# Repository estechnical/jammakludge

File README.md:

# JammaKludge

A simple PCB to insert between Jamma PCBs and the jamma connector to break out test points.

Also provides a kludge space for video filters/impedance matching used to fix ghosting.

That's Jammawang!

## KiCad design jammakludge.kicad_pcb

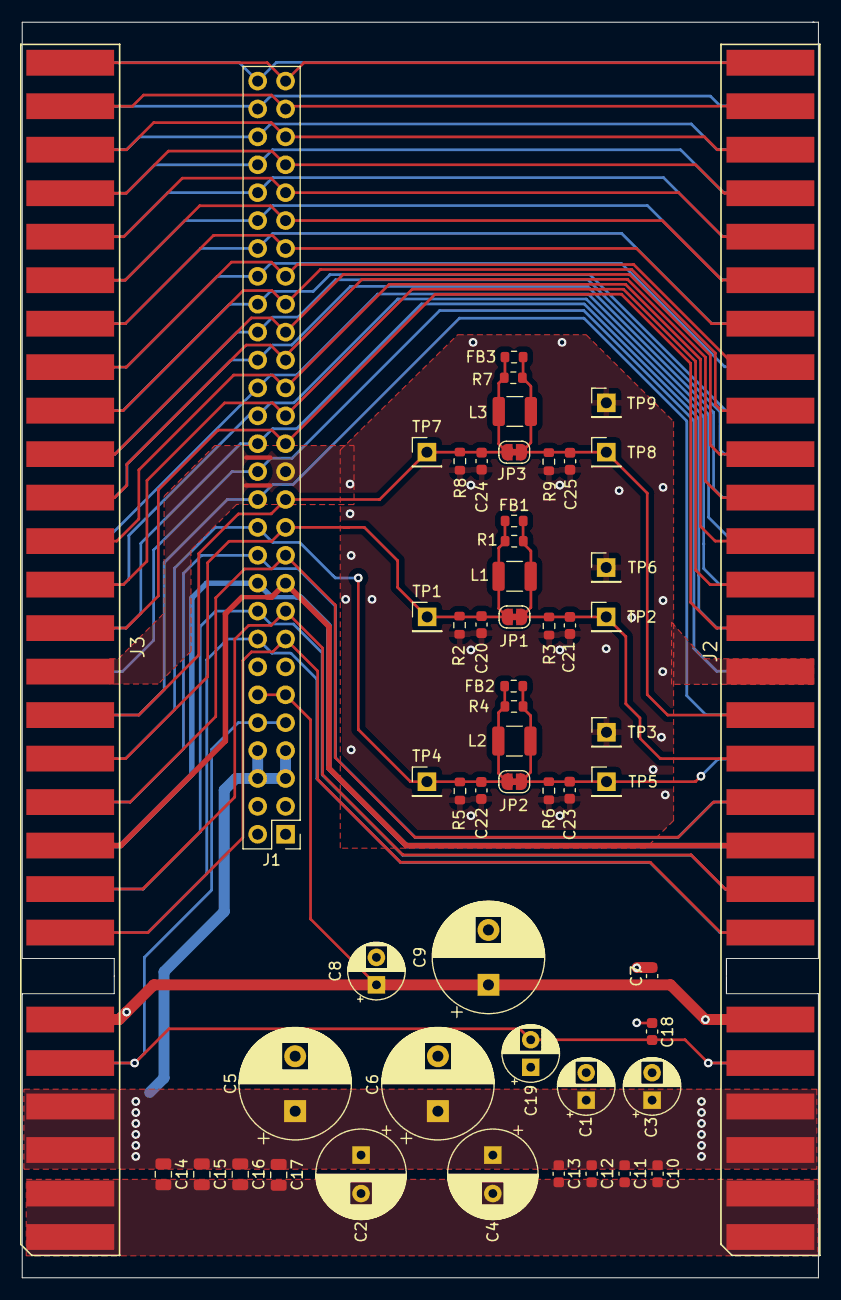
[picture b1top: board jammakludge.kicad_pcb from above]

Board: 2 copper layers, 72.5 x 114.3 mm, 55 parts (0 on the bottom side), 49 nets.

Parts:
C1, C3, C8, C19: C_Polarized; CP_Radial_D5.0mm_P2.50mm
C2, C4: C_Polarized; CP_Radial_D8.0mm_P3.50mm
C5, C6, C9: C_Polarized; CP_Radial_D10.0mm_P5.00mm
C7, C10, C11, C12, C13, C18, C20, C21, C22, C23, C24, C25: C; C_0603_1608Metric
C14, C15, C16, C17: C; C_0805_2012Metric
FB1, FB2, FB3: FerriteBead; R_0603_1608Metric
J1: Conn_02x28_Odd_Even; PinHeader_2x28_P2.54mm_Vertical
J2, J3: Conn_02x28; JAMMA-56
JP1, JP2, JP3: SolderJumper_2_Bridged; SolderJumper-2_P1.3mm_Bridged_RoundedPad1.0x1.5mm
L1, L2, L3: L; R_1210_3225Metric
R1, R2, R3, R4, R5, R6, R7, R8, R9: R; R_0603_1608Metric
TP1, TP2, TP3, TP4, TP5, TP6, TP7, TP8, TP9: TestPoint; PinHeader_1x01_P2.54mm_Vertical

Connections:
+5V: C1.1, C2.1, C3.1, C4.1, C5.1, C6.1, C10.1, C11.1, C12.1, C13.1, C14.1, C15.1, C16.1, C17.1, J1.5, J1.6, J1.7, J1.8, J2.3 (+5v), J2.4 (+5v), J2.C (+5v), J2.D (+5v), J3.3 (+5v), J3.4 (+5v), J3.C (+5v), J3.D (+5v)
+12V: C7.1, C8.1, C9.1, J1.11, J1.12, J2.6 (+12v), J2.F (+12v), J3.6 (+12v), J3.F (+12v)
-5V: C18.1, C19.2, J1.9, J1.10, J2.5 (-5v), J2.E (-5v), J3.5 (-5v), J3.E (-5v)
/Audio_+: J1.21, J2.11 (Audio_+), J3.11 (Audio_+)
/Audio_gnd: J1.22, J2.M (Audio_gnd), J3.M (Audio_gnd)
/Coin_1: J1.31, J2.16 (Coin_1), J3.16 (Coin_1)
/Coin_2: J1.32, J2.T (Coin2), J3.T (Coin2)
/Gnd_27: J1.53, J2.27 (Gnd), J3.27 (Gnd)
/Gnd_28: J1.55, J2.28 (Gnd), J3.28 (Gnd)
/Gnd_e: J1.54, J2.e (Gnd), J3.e (Gnd)
/Gnd_f: J1.56, J2.f (Gnd), J3.f (Gnd)
/Lockout_1: J1.17, J2.9 (Lockout_1), J3.9 (Lockout_1)
/Lockout_2: J1.18, J2.K (Lockout_2), J3.K (Lockout_2)
/Meter_1: J1.15, J2.8 (Meter_1), J3.8 (Meter_1)
/Meter_2: J1.16, J2.J (Meter_2), J3.J (Meter_2)
/Nc_26: J1.51, J2.26 (NC), J3.26 (NC)
/Nc_d: J1.52, J2.d (NC), J3.d (NC)
/P1_button1: J1.43, J2.22 (P1_button1), J3.22 (P1_button1)
/P1_button2: J1.45, J2.23 (P1_button2), J3.23 (P1_button2)
/P1_button3: J1.47, J2.24 (P1_button3), J3.24 (P1_button3)
/P1_button4: J1.49, J2.25 (P1_button4), J3.25 (P1_button4)
/P1_down: J1.37, J2.19 (P1_down), J3.19 (P1_down)
/P1_left: J1.39, J2.20 (P1_left), J3.20 (P1_left)
/P1_right: J1.41, J2.21 (P1_right), J3.21 (P1_right)
/P1_start: J1.33, J2.17 (P1_start), J3.17 (P1_start)
/P1_up: J1.35, J2.18 (P1_up), J3.18 (P1_up)
/P2_button1: J1.44, J2.Z (P2_button1), J3.Z (P2_button1)
/P2_button2: J1.46, J2.a (P2_button2), J3.a (P2_button2)
/P2_button3: J1.48, J2.b (P2_button3), J3.b (P2_button3)
/P2_button4: J1.50, J2.c (P2_button4), J3.c (P2_button4)
/P2_down: J1.38, J2.W (P2_down), J3.W (P2_down)
/P2_left: J1.40, J2.X (P2_left), J3.X (P2_left)
/P2_right: J1.42, J2.Y (P2_right), J3.Y (P2_right)
/P2_start: J1.34, J2.U (P2_start), J3.U (P2_start)
/P2_up: J1.36, J2.V (P2_up), J3.V (P2_up)
/Service_switch: J1.28, J2.R (Service_switch), J3.R (Service_switch)
/Speaker_+: J1.19, J2.10 (Speaker_+), J3.10 (Speaker_+)
/Speaker_-: J1.20, J2.L (Speaker_-), J3.L (Speaker_-)
/Test_switch: J1.29, J2.15 (Test_switch), J3.15 (Test_switch)
/Tilt_switch: J1.30, J2.S (Tilt_switch), J3.S (Tilt_switch)
/VidBlue: C25.1, FB3.2, J2.13 (Video_blue), JP3.2 (B), L3.2, R7.2, R9.2, TP8.1
/VidBlueIn: C24.1, FB3.1, J1.25, J3.13 (Video_blue), JP3.1 (A), L3.1, R7.1, R8.2, TP7.1
/VidGnd: C20.2, C21.2, C22.2, C23.2, C24.2, C25.2, J1.27, J2.14 (Video_gnd), J3.14 (Video_gnd), R2.1, R3.1, R5.1, R6.1, R8.1, R9.1, TP3.1, TP6.1, TP9.1
/VidGreen: C23.1, FB2.2, J2.N (Video_green), JP2.2 (B), L2.2, R4.2, R6.2, TP5.1
/VidGreenIn: C22.1, FB2.1, J1.24, J3.N (Video_green), JP2.1 (A), L2.1, R4.1, R5.2, TP4.1
/VidRed: C21.1, FB1.2, J2.12 (Video_red), JP1.2 (B), L1.2, R1.2, R3.2, TP2.1
/VidRedIn: C20.1, FB1.1, J1.23, J3.12 (Video_red), JP1.1 (A), L1.1, R1.1, R2.2, TP1.1
/VidSync: J1.26, J2.P (Video_sync), J3.P (Video_sync)
GND: C1.2, C2.2, C3.2, C4.2, C5.2, C6.2, C7.2, C8.2, C9.2, C10.2, C11.2, C12.2, C13.2, C14.2, C15.2, C16.2, C17.2, C18.2, C19.1, J1.1, J1.2, J1.3, J1.4, J2.1 (Gnd), J2.2 (Gnd), J2.A (Gnd), J2.B (Gnd), J3.1 (Gnd), J3.2 (Gnd), J3.A (Gnd), J3.B (Gnd)

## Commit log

2020-11-17 Initial commit - not even close to useful. :)
2020-11-17 Added a readme
2020-11-18 Jamma symbol and footprint added. Power supply caps added to schematic.
2020-11-20 Progress with labels and footprints
2020-11-21 Added more power bypassing capacitors to 5v and 12v supplies.
2020-11-22 Added test points/breakout points for video filter input and output
2020-11-22 labels added
2020-12-03 Mostly completed layout, fixed some labels that didn't match right. Left to do: better gnd stitching and tidy up
2020-12-05 Layout is basically complete, missing outline until dimensions can be double checked. DRC violations minimised but footprints (solder jumper and jamma edge connector) cause violations.
2020-12-05 added outline
